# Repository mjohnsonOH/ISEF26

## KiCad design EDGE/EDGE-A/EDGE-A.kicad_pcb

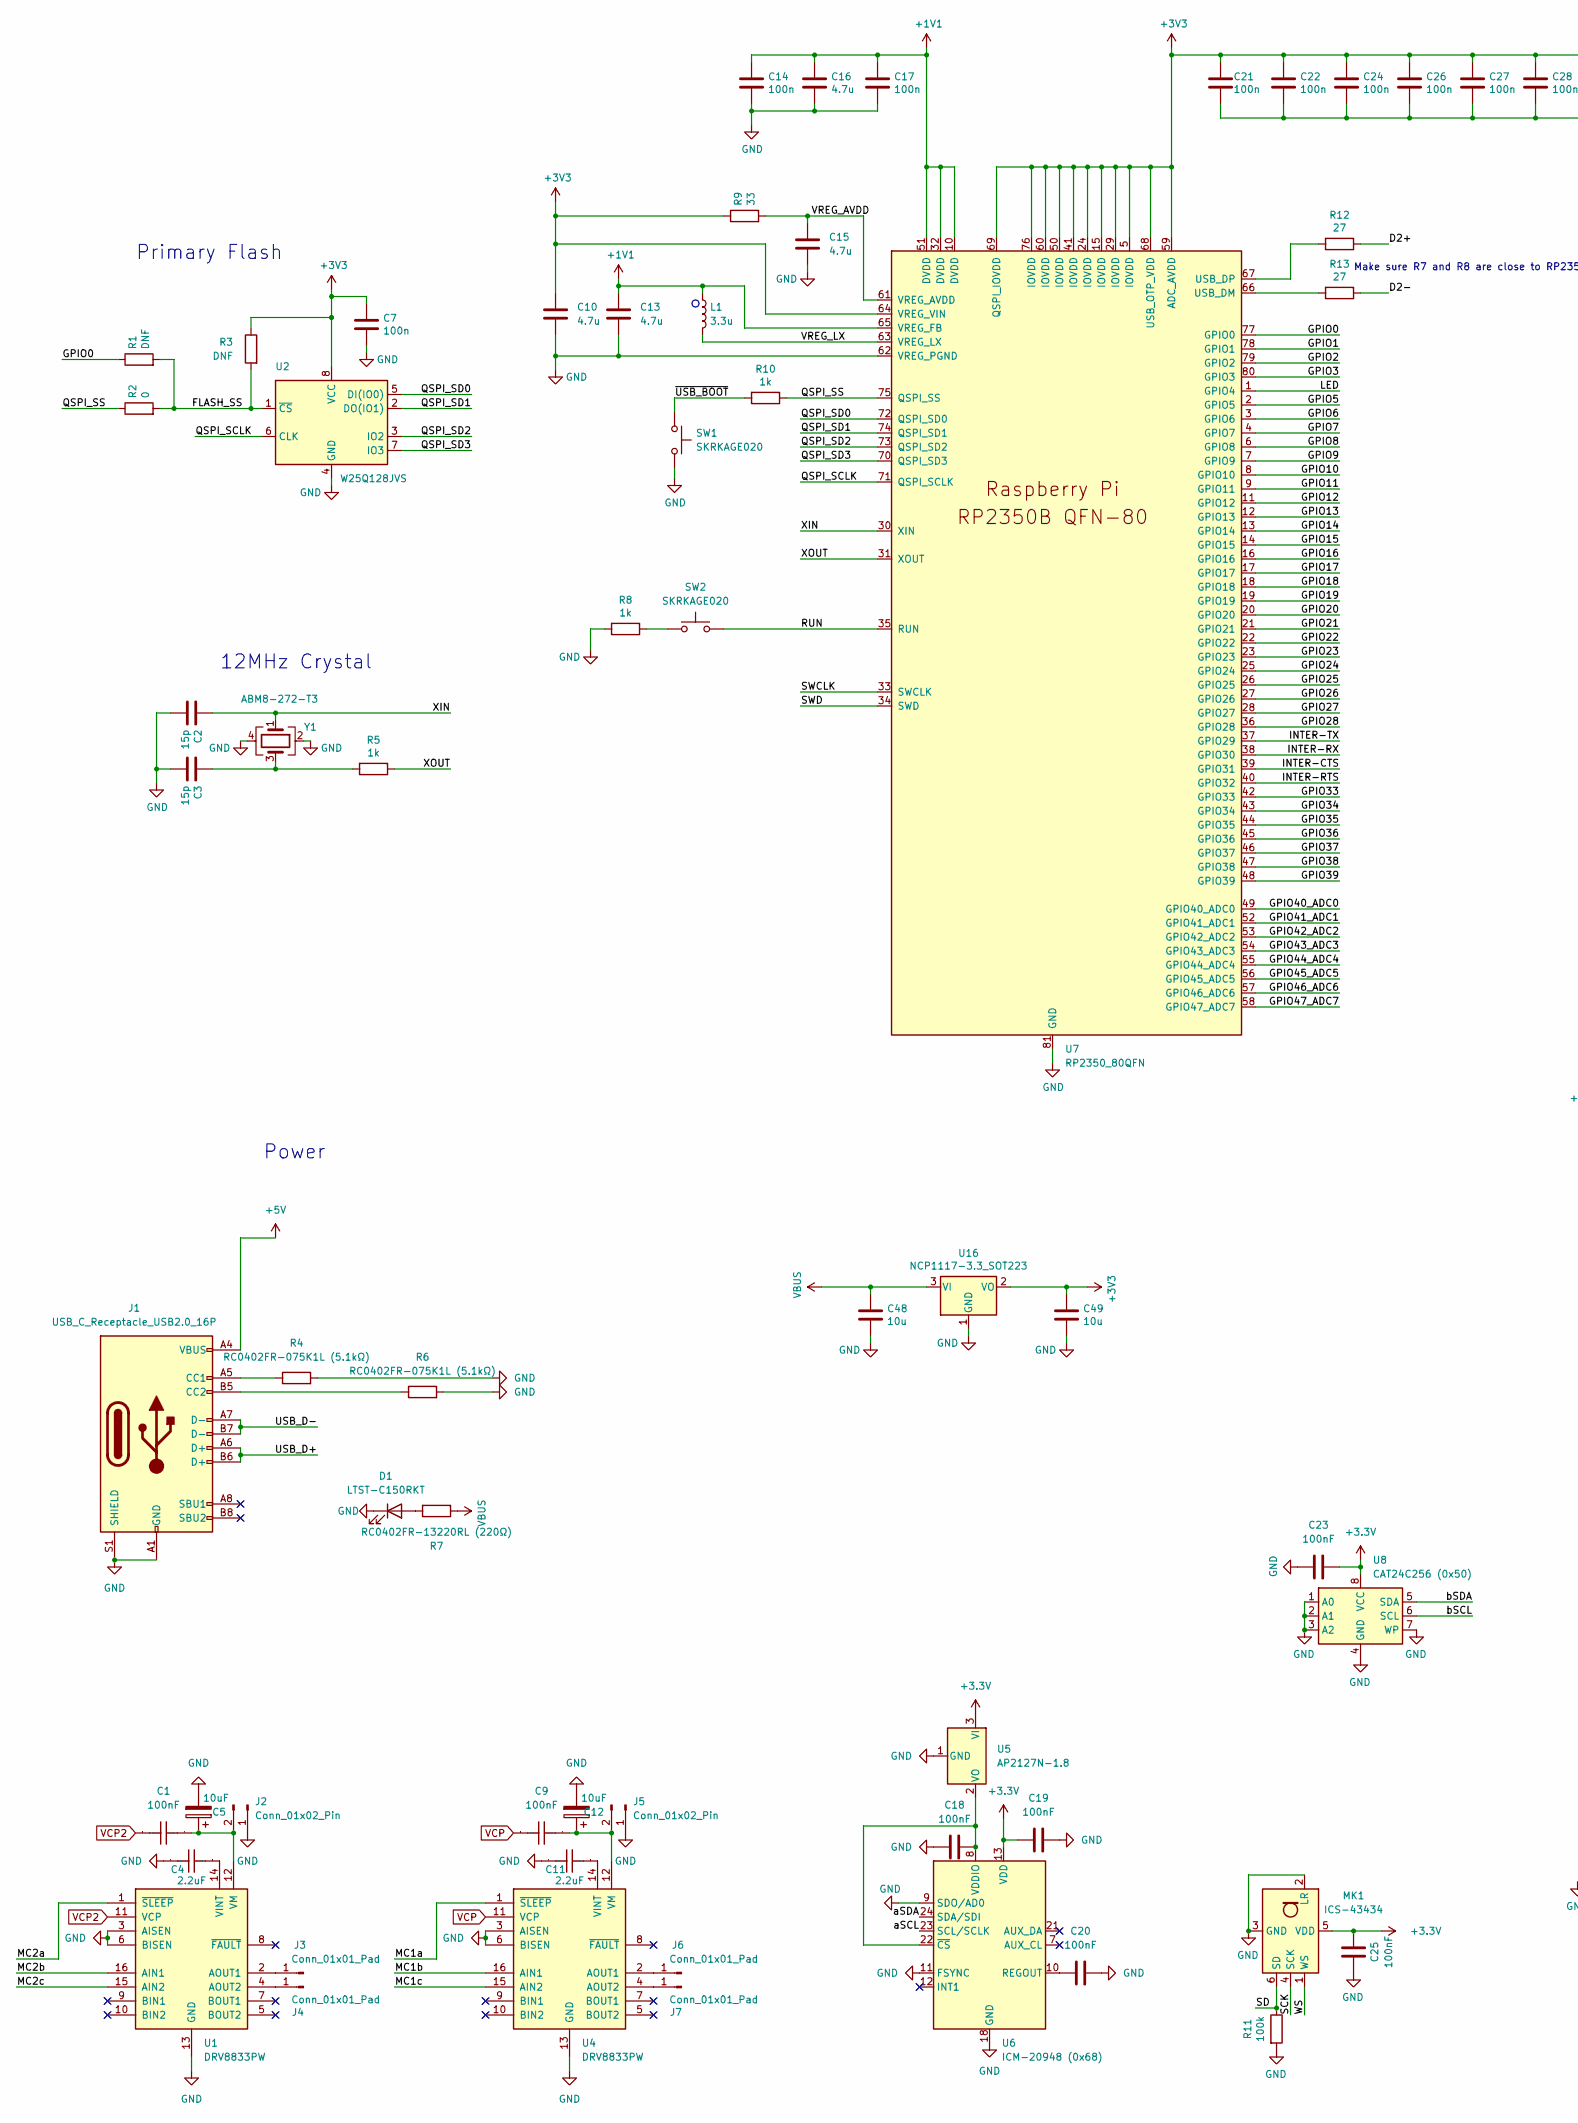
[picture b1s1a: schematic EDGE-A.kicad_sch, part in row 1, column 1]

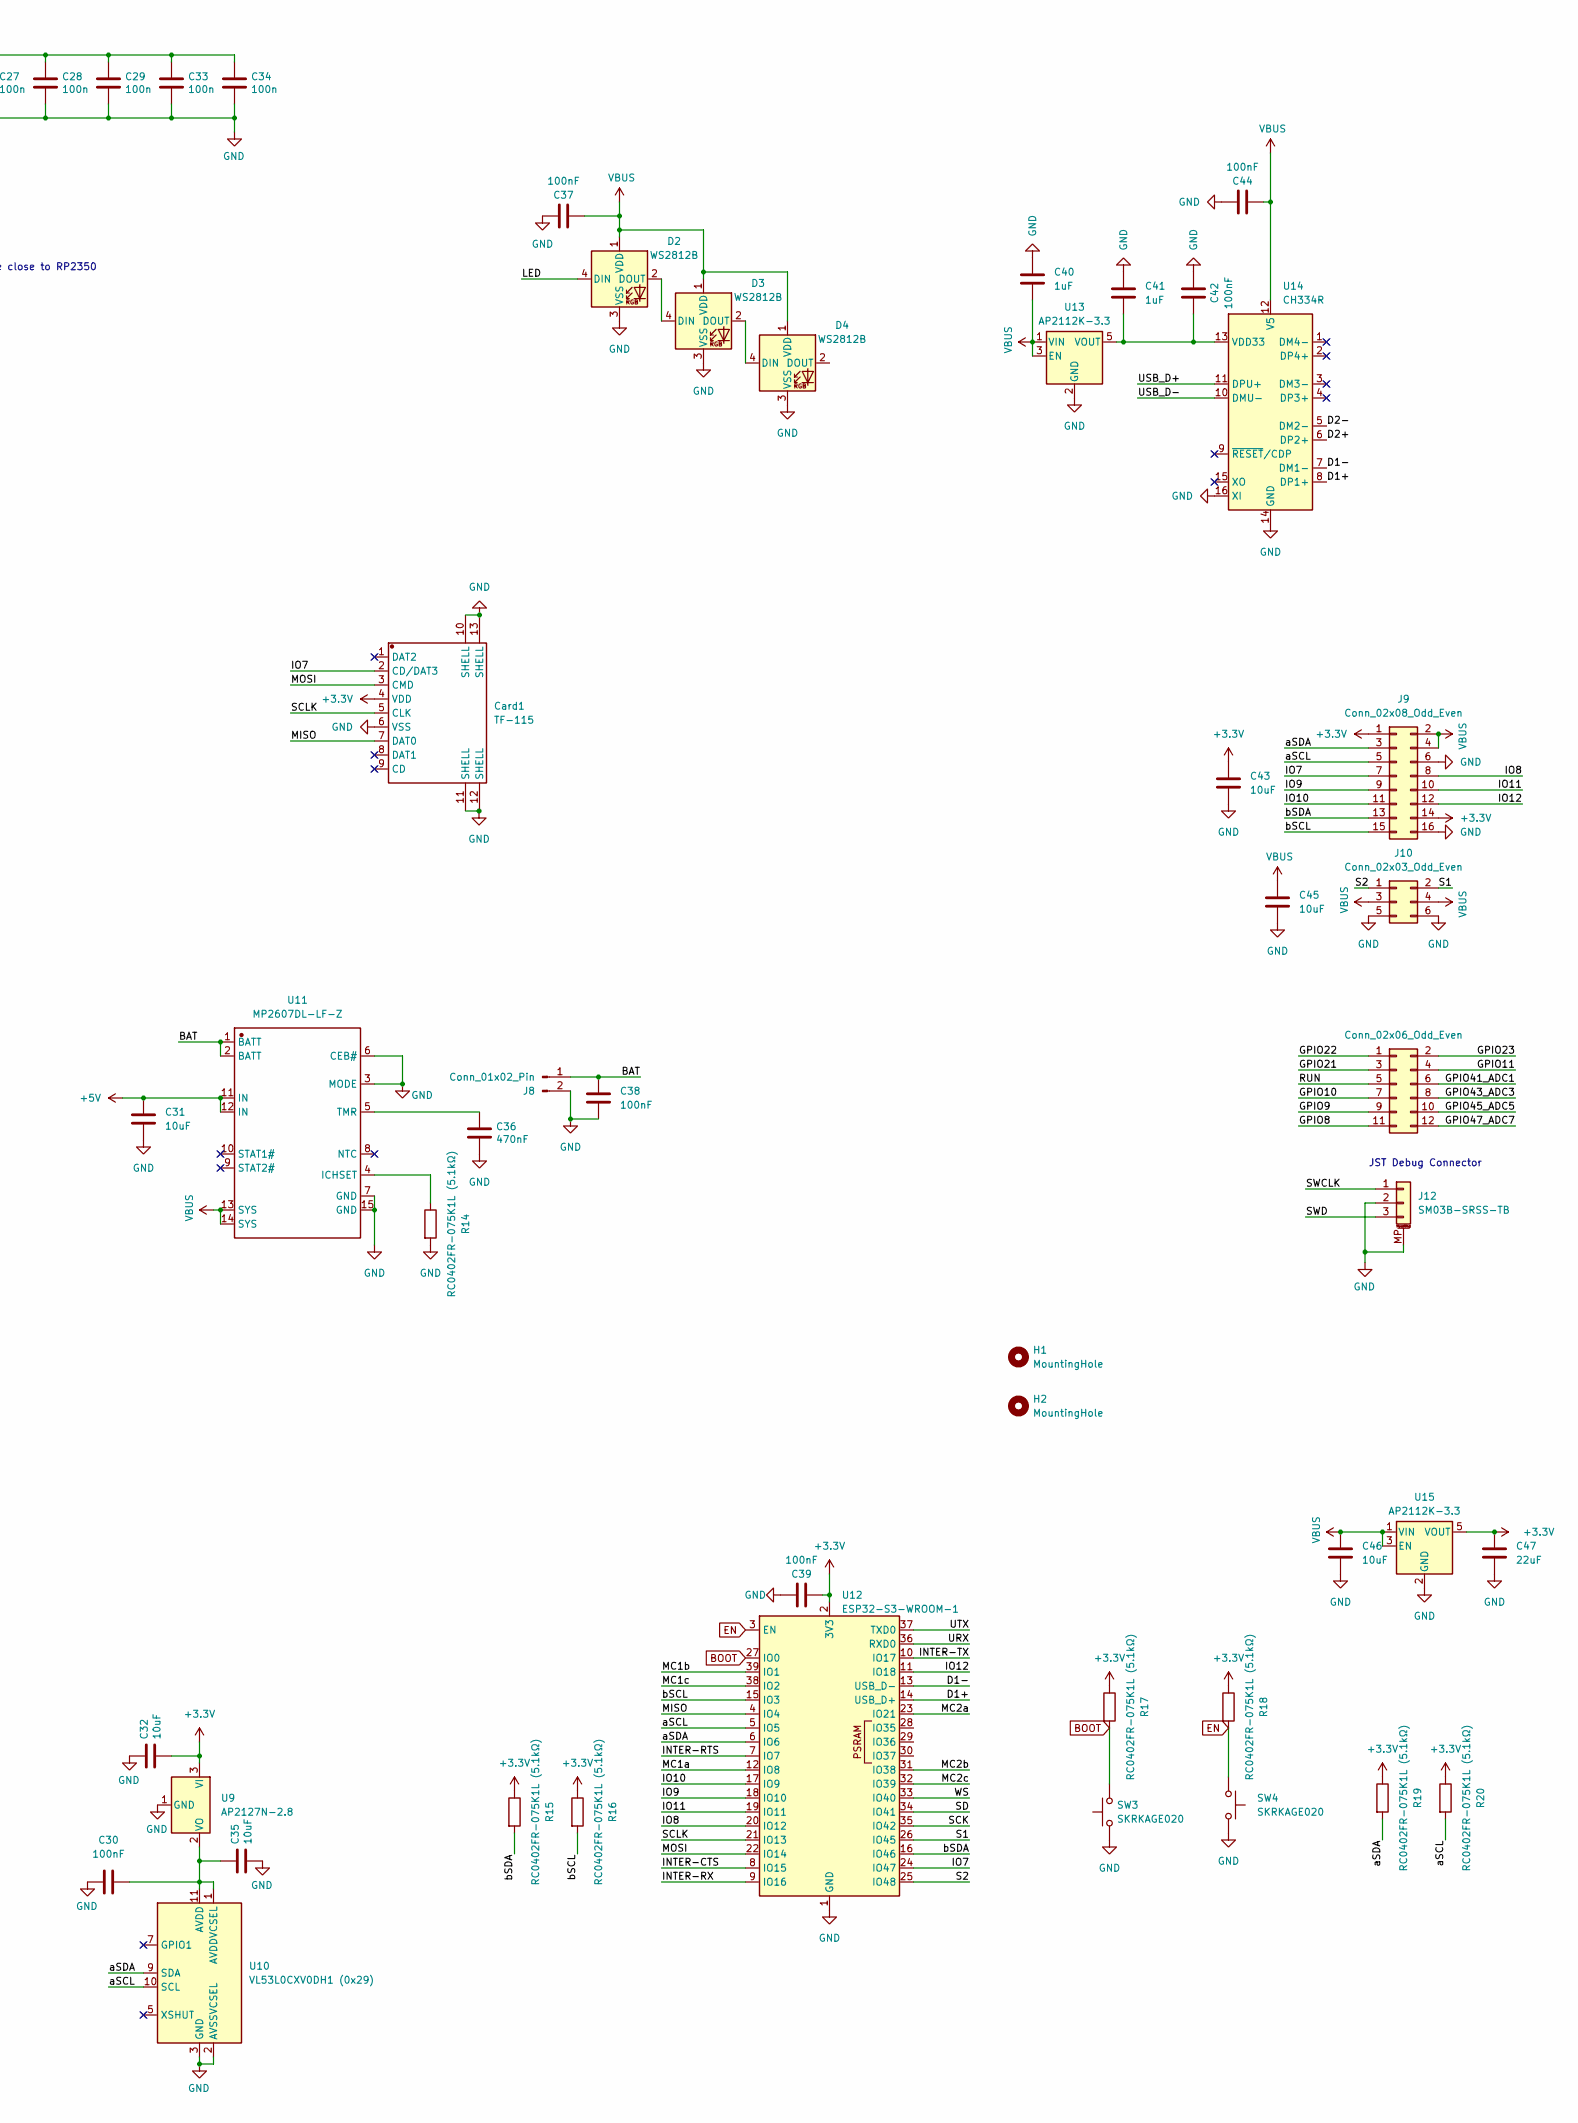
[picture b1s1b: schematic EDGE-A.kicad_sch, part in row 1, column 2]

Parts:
C1, C9: 100nF; CC0805KRX7R9BB104; Manufacturer Part CC0805KRX7R9BB104
C2, C3: 15p; C_0402_1005Metric
C4, C11: 2.2uF; GRM155R60J225KE01D; Manufacturer Part GRM155R60J225KE01D
C5, C12: 10uF; TAJA106K016RNJ
C7, C14, C17, C21, C22, C24, C26, C27, C28, C29, C33, C34: 100n; C_0402_1005Metric
C10, C13: 4.7u; C_0402_1005Metric_small_pads
C15, C16: 4.7u; C_0402_1005Metric
C18, C19, C20, C23, C25, C30, C37, C38, C39, C42, C44: 100nF; C0402
C31, C43, C45, C46: 10uF; C0402
C32, C35: 10uF; C_0805_2012Metric
C36: 470nF; C_0402_1005Metric
C40, C41: 1uF; C0402
C47: 22uF; C0402
C48, C49: 10u; C_0805_2012Metric
Card1: TF-115; TF-SMD_TF-115; Manufacturer Part TF-115
D1: LTST-C150RKT; LED_1206_3216Metric
D2, D3, D4: WS2812B; LED_WS2812B_PLCC4_5.0x5.0mm_P3.2mm
H1, H2: MountingHole; MountingHole_3.2mm_M3
J1: USB_C_Receptacle_USB2.0_16P; USB_C_Receptacle_HCTL_HC-TYPE-C-16P-01A
J2, J5: Conn_01x02_Pin; PinHeader_1x02_P2.54mm_Vertical
J3, J4, J6, J7: Conn_01x01_Pad; TestPoint_Pad_1.5x1.5mm
J8: Conn_01x02_Pin; JST_PH_S2B-PH-K_1x02_P2.00mm_Horizontal
J9: Conn_02x08_Odd_Even; PinHeader_2x08_P2.54mm_Vertical
J10: Conn_02x03_Odd_Even; PinHeader_2x03_P2.54mm_Vertical
J11: Conn_02x06_Odd_Even; PinHeader_2x06_P2.54mm_Vertical
J12: SM03B-SRSS-TB; JST_SH_SM03B-SRSS-TB_1x03-1MP_P1.00mm_Horizontal
L1: 3.3u; L_pol_2016
MK1: ICS-43434; InvenSense_ICS-43434-6_3.5x2.65mm
R1, R3: DNF; R_0402_1005Metric
R2: 0; R_0402_1005Metric
R4, R6, R14, R15, R16, R17, R18, R19, R20: RC0402FR-075K1L (5.1kΩ); R0402
R5, R8, R10: 1k; R_0402_1005Metric
R7: RC0402FR-13220RL (220Ω); R0402
R9: 33; R_0402_1005Metric
R11: 100k; R_0402_1005Metric
R12, R13: 27; R_0402_1005Metric
SW1, SW2, SW3, SW4: SKRKAGE020; SW_Push_SPST_NO_Alps_SKRK
U1, U4: DRV8833PW; TSSOP-16_4.4x5mm_P0.65mm
U2: W25Q128JVS; SOIC-8_5.3x5.3mm_P1.27mm
U5: AP2127N-1.8; SOT-23
U6: ICM-20948 (0x68); InvenSense_QFN-24_3x3mm_P0.4mm
U7: RP2350_80QFN; RP2350-QFN-80-1EP_10x10_P0.4mm_EP3.4x3.4mm_ThermalVias
U8: CAT24C256 (0x50); SOIC-8_3.9x4.9mm_P1.27mm
U9: AP2127N-2.8; SOT-23
U10: VL53L0CXV0DH1 (0x29); ST_VL53L1x
U11: MP2607DL-LF-Z; MP2607DL; Manufacturer Part MP2607DL-LF-Z
U12: ESP32-S3-WROOM-1
U13, U15: AP2112K-3.3; SOT-23-5
U14: CH334R; QSOP-16_3.9x4.9mm_P0.635mm
U16: NCP1117-3.3_SOT223; SOT-223-3_TabPin2
Y1: ABM8-272-T3; Crystal_SMD_3225-4Pin_3.2x2.5mm

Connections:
+1V1: C13.1, C14.1, C16.1, C17.1, L1.1, U7.10 (DVDD), U7.32 (DVDD), U7.51 (DVDD), U7.65 (VREG_FB)
+3.3V: C19.1, C23.1, C25.1, C32.2, C39.2, C43.1, C47.1, Card1.4 (VDD), J9.1, J9.14, MK1.5 (VDD), R15.1, R16.1, R17.1, R18.1, R19.1, R20.1, U5.3 (VI), U6.13 (VDD), U8.8 (VCC), U9.3 (VI), U12.2 (3V3), U15.5 (VOUT)
+3V3: C7.1, C10.1, C21.1, C22.1, C24.1, C26.1, C27.1, C28.1, C29.1, C33.1, C34.1, C49.1, R3.1, R9.1, U2.8 (VCC), U7.5 (IOVDD), U7.15 (IOVDD), U7.24 (IOVDD), U7.29 (IOVDD), U7.41 (IOVDD), U7.50 (IOVDD), U7.59 (ADC_AVDD), U7.60 (IOVDD), U7.64 (VREG_VIN), U7.68 (USB_OTP_VDD), U7.69 (QSPI_IOVDD), U7.76 (IOVDD), U16.2 (VO)
+5V: C31.1, J1.A4 (VBUS), J1.A9 (VBUS), J1.B4 (VBUS), J1.B9 (VBUS), U11.11 (IN), U11.12 (IN)
/BAT: C38.1, J8.1, U11.1 (BATT), U11.2 (BATT)
/D1+: U12.14 (USB_D+), U14.8 (DP1+)
/D1-: U12.13 (USB_D-), U14.7 (DM1-)
/D2+: R12.1, U14.6 (DP2+)
/D2-: R13.1, U14.5 (DM2-)
/FLASH_SS: R1.2, R2.2, R3.2, U2.1 (~CS)
/GPIO0: R1.1, U7.77 (GPIO0)
/GPIO1: U7.78 (GPIO1)
/GPIO2: U7.79 (GPIO2)
/GPIO3: U7.80 (GPIO3)
/GPIO5: U7.2 (GPIO5)
/GPIO6: U7.3 (GPIO6)
/GPIO7: U7.4 (GPIO7)
/GPIO8: J11.11, U7.6 (GPIO8)
/GPIO9: J11.9, U7.7 (GPIO9)
/GPIO10: J11.7, U7.8 (GPIO10)
/GPIO11: J11.4, U7.9 (GPIO11)
/GPIO12: U7.11 (GPIO12)
/GPIO13: U7.12 (GPIO13)
/GPIO14: U7.13 (GPIO14)
/GPIO15: U7.14 (GPIO15)
/GPIO16: U7.16 (GPIO16)
/GPIO17: U7.17 (GPIO17)
/GPIO18: U7.18 (GPIO18)
/GPIO19: U7.19 (GPIO19)
/GPIO20: U7.20 (GPIO20)
/GPIO21: J11.3, U7.21 (GPIO21)
/GPIO22: J11.1, U7.22 (GPIO22)
/GPIO23: J11.2, U7.23 (GPIO23)
/GPIO24: U7.25 (GPIO24)
/GPIO25: U7.26 (GPIO25)
/GPIO26: U7.27 (GPIO26)
/GPIO27: U7.28 (GPIO27)
/GPIO28: U7.36 (GPIO28)
/GPIO33: U7.42 (GPIO33)
/GPIO34: U7.43 (GPIO34)
/GPIO35: U7.44 (GPIO35)
/GPIO36: U7.45 (GPIO36)
/GPIO37: U7.46 (GPIO37)
/GPIO38: U7.47 (GPIO38)
/GPIO39: U7.48 (GPIO39)
/GPIO40_ADC0: U7.49 (GPIO40_ADC0)
/GPIO41_ADC1: J11.6, U7.52 (GPIO41_ADC1)
/GPIO42_ADC2: U7.53 (GPIO42_ADC2)
/GPIO43_ADC3: J11.8, U7.54 (GPIO43_ADC3)
/GPIO44_ADC4: U7.55 (GPIO44_ADC4)
/GPIO45_ADC5: J11.10, U7.56 (GPIO45_ADC5)
/GPIO46_ADC6: U7.57 (GPIO46_ADC6)
/GPIO47_ADC7: J11.12, U7.58 (GPIO47_ADC7)
/INTER-CTS: U7.39 (GPIO31), U12.8 (IO15)
/INTER-RTS: U7.40 (GPIO32), U12.7 (IO7)
/INTER-RX: U7.38 (GPIO30), U12.9 (IO16)
/INTER-TX: U7.37 (GPIO29), U12.10 (IO17)
/IO7: Card1.2 (CD/DAT3), J9.7, U12.24 (IO47)
/IO8: J9.8, U12.20 (IO12)
/IO9: J9.9, U12.18 (IO10)
/IO10: J9.11, U12.17 (IO9)
/IO11: J9.10, U12.19 (IO11)
/IO12: J9.12, U12.11 (IO18)
/LED: D2.4 (DIN), U7.1 (GPIO4)
/MC1a: U4.1 (~SLEEP), U12.12 (IO8)
/MC1b: U4.16 (AIN1), U12.39 (IO1)
/MC1c: U4.15 (AIN2), U12.38 (IO2)
/MC2a: U1.1 (~SLEEP), U12.23 (IO21)
/MC2b: U1.16 (AIN1), U12.31 (IO38)
/MC2c: U1.15 (AIN2), U12.32 (IO39)
/MISO: Card1.7 (DAT0), U12.4 (IO4)
/MOSI: Card1.3 (CMD), U12.22 (IO14)
/QSPI_SCLK: U2.6 (CLK), U7.71 (QSPI_SCLK)
/QSPI_SD0: U2.5 (DI(IO0)), U7.72 (QSPI_SD0)
/QSPI_SD1: U2.2 (DO(IO1)), U7.74 (QSPI_SD1)
/QSPI_SD2: U2.3 (IO2), U7.73 (QSPI_SD2)
/QSPI_SD3: U2.7 (IO3), U7.70 (QSPI_SD3)
/QSPI_SS: R2.1, R10.1, U7.75 (QSPI_SS)
/RUN: J11.5, SW2.2, U7.35 (RUN)
/S1: J10.2, U12.26 (IO45)
/S2: J10.1, U12.25 (IO48)
/SCK: MK1.4 (SCK), U12.35 (IO42)
/SCLK: Card1.5 (CLK), U12.21 (IO13)
/SD: MK1.6 (SD), R11.1, U12.34 (IO41)
/SWCLK: J12.1, U7.33 (SWCLK)
/SWD: J12.3, U7.34 (SWD)
/URX: U12.36 (RXD0)
/USB_D+: J1.A6 (D+), J1.B6 (D+), U14.11 (DPU+)
/USB_D-: J1.A7 (D-), J1.B7 (D-), U14.10 (DMU-)
/UTX: U12.37 (TXD0)
/VREG_AVDD: C15.1, R9.2, U7.61 (VREG_AVDD)
/VREG_LX: L1.2, U7.63 (VREG_LX)
/WS: MK1.1 (WS), U12.33 (IO40)
/XIN: C2.1, U7.30 (XIN), Y1.1
/XOUT: R5.1, U7.31 (XOUT)
/aSCL: J9.5, R20.2, U6.23 (SCL/SCLK), U10.10 (SCL), U12.5 (IO5)
/aSDA: J9.3, R19.2, U6.24 (SDA/SDI), U10.9 (SDA), U12.6 (IO6)
/bSCL: J9.15, R16.2, U8.6 (SCL), U12.15 (IO3)
/bSDA: J9.13, R15.2, U8.5 (SDA), U12.16 (IO46)
/~USB_BOOT: R10.2, SW1.1
BOOT: R17.2, SW3.2, U12.27 (IO0)
EN: R18.2, SW4.1, U12.3 (EN)
GND: C2.2, C3.2, C4.2, C5.2, C7.2, C10.2, C11.2, C12.2, C13.2, C14.2, C15.2, C16.2, C17.2, C18.1, C19.2, C20.2, C21.2, C22.2, C23.2, C24.2, C25.2, C26.2, C27.2, C28.2, C29.2, C30.2, C31.2, C32.1, C33.2, C34.2, C35.2, C36.2, C37.1, C38.2, C39.1, C40.1, C41.1, C42.1, C43.2, C44.1, C45.2, C46.2, C47.2, C48.2, C49.2, Card1.6 (VSS), Card1.10 (SHELL), Card1.11 (SHELL), Card1.12 (SHELL), Card1.13 (SHELL), D1.1 (K), D2.3 (VSS), D3.3 (VSS), D4.3 (VSS), J1.A1 (GND), J1.A12 (GND), J1.B1 (GND), J1.B12 (GND), J1.S1 (SHIELD), J2.1, J5.1, J8.2, J9.6, J9.16, J10.5, J10.6, J12.2, J12.MP (MountPin), MK1.2 (LR), MK1.3 (GND), R4.2, R6.2, R8.2, R11.2, R14.2, SW1.2, SW3.1, SW4.2, U1.3 (AISEN), U1.6 (BISEN), U1.13 (GND), U2.4 (GND), U4.3 (AISEN), U4.6 (BISEN), U4.13 (GND), U5.1 (GND), U6.9 (SDO/AD0), U6.11 (FSYNC), U6.18 (GND), U6.20 (GND), U7.62 (VREG_PGND), U7.81 (GND), U8.1 (A0), U8.2 (A1), U8.3 (A2), U8.4 (GND), U8.7 (WP), U9.1 (GND), U10.2 (AVSSVCSEL), U10.3 (GND), U10.4 (GND), U10.6 (GND), U10.12 (GND), U11.3 (MODE), U11.6 (CEB#), U11.7 (GND), U11.15 (GND), U12.1 (GND), U12.40 (GND), U12.41 (GND), U13.2 (GND), U14.14 (GND), U14.16 (XI), U15.2 (GND), U16.1 (GND), Y1.2, Y1.4
unnamed: C3.1, R5.2, Y1.3
unnamed: D1.2 (A), R7.2
unnamed: D2.2 (DOUT), D3.4 (DIN)
unnamed: D3.2 (DOUT), D4.4 (DIN)
unnamed: J1.A5 (CC1), R4.1
unnamed: J1.B5 (CC2), R6.1
unnamed: C1.2, C5.1, J2.2, U1.12 (VM)
unnamed: J3.1, U1.2 (AOUT1)
unnamed: J4.1, U1.4 (AOUT2)
unnamed: C9.2, C12.1, J5.2, U4.12 (VM)
unnamed: J6.1, U4.2 (AOUT1)
unnamed: J7.1, U4.4 (AOUT2)
unnamed: R8.1, SW2.1
unnamed: C4.1, U1.14 (VINT)
unnamed: C11.1, U4.14 (VINT)
unnamed: C18.2, U5.2 (VO), U6.8 (VDDIO), U6.22 (~CS)
unnamed: C20.1, U6.10 (REGOUT)
unnamed: R13.2, U7.66 (USB_DM)
unnamed: R12.2, U7.67 (USB_DP)
unnamed: C30.1, C35.1, U9.2 (VO), U10.1 (AVDDVCSEL), U10.11 (AVDD)
unnamed: R14.1, U11.4 (ICHSET)
unnamed: C36.1, U11.5 (TMR)
unnamed: C41.2, C42.2, U13.5 (VOUT), U14.13 (VDD33)
VBUS: C37.2, C40.2, C44.2, C45.1, C46.1, C48.1, D2.1 (VDD), D3.1 (VDD), D4.1 (VDD), J9.2, J9.4, J10.3, J10.4, R7.1, U11.13 (SYS), U11.14 (SYS), U13.1 (VIN), U13.3 (EN), U14.12 (V5), U15.1 (VIN), U15.3 (EN), U16.3 (VI)
VCP: C9.1, U4.11 (VCP)
VCP2: C1.1, U1.11 (VCP)

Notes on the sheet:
Power
12MHz Crystal
Make sure R7 and R8 are close to RP2350
JST Debug Connector
Primary Flash

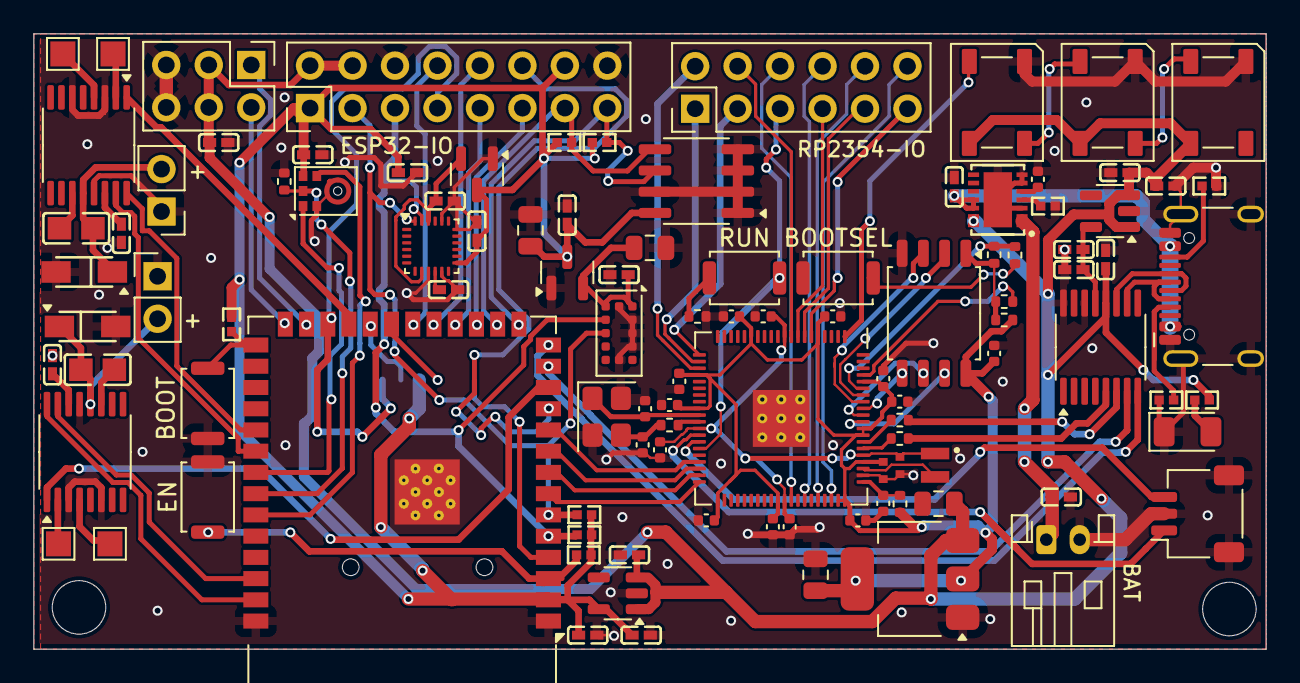
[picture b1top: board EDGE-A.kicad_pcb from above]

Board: 2 copper layers, 73.7 x 36.8 mm, 108 parts (1 on the bottom side), 96 nets.

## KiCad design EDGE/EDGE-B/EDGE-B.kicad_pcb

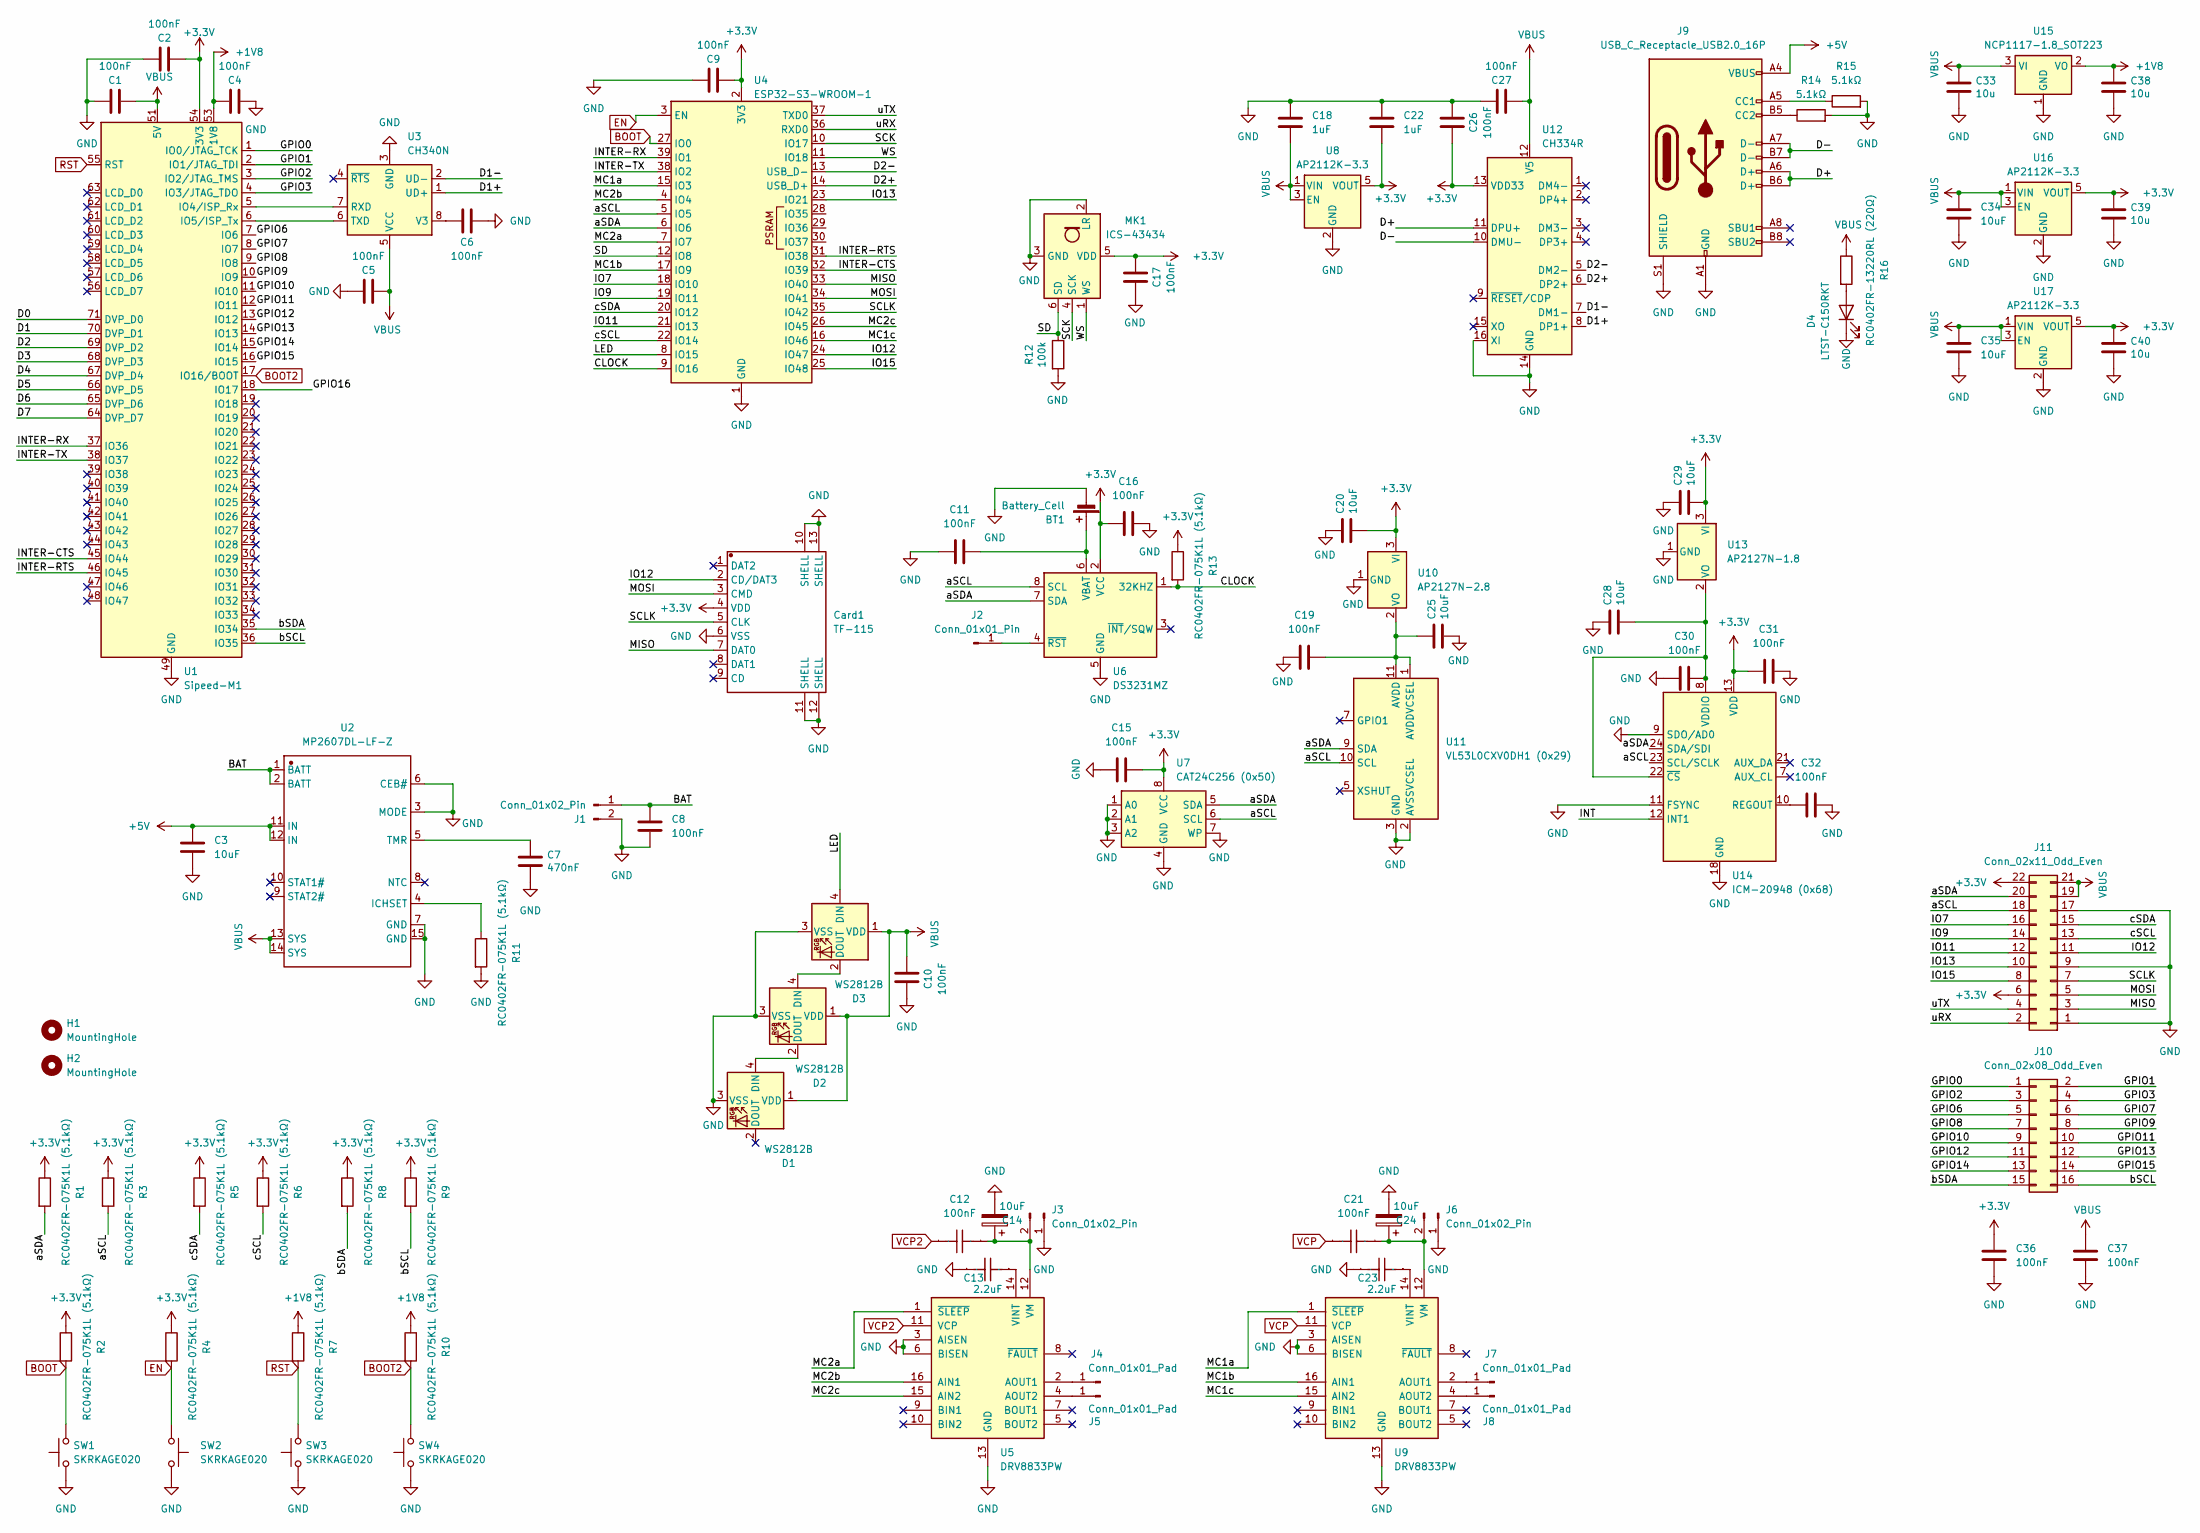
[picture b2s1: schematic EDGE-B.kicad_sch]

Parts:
BT1: Battery_Cell; BatteryHolder_Keystone_3000_1x12mm
C1, C2, C4, C5, C6, C8, C9, C10, C11, C15, C16, C17, C19, C26, C27, C30, C31, C32, C36, C37: 100nF; C0402
C3, C34, C35: 10uF; C0402
C7: 470nF; C_0402_1005Metric
C12, C21: 100nF; CC0805KRX7R9BB104; Manufacturer Part CC0805KRX7R9BB104
C13, C23: 2.2uF; GRM155R60J225KE01D; Manufacturer Part GRM155R60J225KE01D
C14, C24: 10uF; TAJA106K016RNJ
C18, C22: 1uF; C0402
C20, C25, C28, C29: 10uF; C_0805_2012Metric
C33, C38, C39, C40: 10u; C_0805_2012Metric
Card1: TF-115; TF-SMD_TF-115; Manufacturer Part TF-115
D1, D2, D3: WS2812B; LED_WS2812B_PLCC4_5.0x5.0mm_P3.2mm
D4: LTST-C150RKT; LED_1206_3216Metric
H1, H2: MountingHole; MountingHole_3.2mm_M3
J1: Conn_01x02_Pin; JST_PH_S2B-PH-K_1x02_P2.00mm_Horizontal
J2: Conn_01x01_Pin; TestPoint_Pad_1.0x1.0mm
J3, J6: Conn_01x02_Pin; PinHeader_1x02_P2.54mm_Vertical
J4, J5, J7, J8: Conn_01x01_Pad; TestPoint_Pad_1.5x1.5mm
J9: USB_C_Receptacle_USB2.0_16P; USB_C_Receptacle_HCTL_HC-TYPE-C-16P-01A
J10: Conn_02x08_Odd_Even; PinHeader_2x08_P2.54mm_Vertical
J11: Conn_02x11_Odd_Even; PinHeader_2x11_P2.54mm_Vertical
MK1: ICS-43434; InvenSense_ICS-43434-6_3.5x2.65mm
R1, R2, R3, R4, R5, R6, R7, R8, R9, R10, R11, R13: RC0402FR-075K1L (5.1kΩ); R0402
R12: 100k; R_0402_1005Metric
R14, R15: 5.1kΩ; R0402
R16: RC0402FR-13220RL (220Ω); R0402
SW1, SW2, SW3, SW4: SKRKAGE020; SW_Push_SPST_NO_Alps_SKRK
U1: Sipeed-M1
U2: MP2607DL-LF-Z; MP2607DL; Manufacturer Part MP2607DL-LF-Z
U3: CH340N; SOP-8_3.9x4.9mm_P1.27mm
U4: ESP32-S3-WROOM-1
U5, U9: DRV8833PW; TSSOP-16_4.4x5mm_P0.65mm
U6: DS3231MZ; SOIC-8_3.9x4.9mm_P1.27mm
U7: CAT24C256 (0x50); SOIC-8_3.9x4.9mm_P1.27mm
U8, U16, U17: AP2112K-3.3; SOT-23-5
U10: AP2127N-2.8; SOT-23
U11: VL53L0CXV0DH1 (0x29); ST_VL53L1x
U12: CH334R; QSOP-16_3.9x4.9mm_P0.635mm
U13: AP2127N-1.8; SOT-23
U14: ICM-20948 (0x68); InvenSense_QFN-24_3x3mm_P0.4mm
U15: NCP1117-1.8_SOT223; SOT-223-3_TabPin2

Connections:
+1V8: C4.1, C38.1, R7.1, R10.1, U1.53 (1V8), U15.2 (VO)
+3.3V: C2.2, C9.2, C15.1, C16.1, C17.1, C20.2, C22.2, C26.2, C29.2, C31.1, C36.1, C39.1, C40.1, Card1.4 (VDD), J11.6, J11.22, MK1.5 (VDD), R1.1, R2.1, R3.1, R4.1, R5.1, R6.1, R8.1, R9.1, R13.1, U1.54 (3V3), U4.2 (3V3), U6.2 (VCC), U7.8 (VCC), U8.5 (VOUT), U10.3 (VI), U12.13 (VDD33), U13.3 (VI), U14.13 (VDD), U16.5 (VOUT), U17.5 (VOUT)
+5V: C3.1, J9.A4 (VBUS), J9.A9 (VBUS), J9.B4 (VBUS), J9.B9 (VBUS), U2.11 (IN), U2.12 (IN)
/BAT: C8.1, J1.1, U2.1 (BATT), U2.2 (BATT)
/CLOCK: R13.2, U4.9 (IO16), U6.1 (32KHZ)
/D0: U1.71 (DVP_D0)
/D1: U1.70 (DVP_D1)
/D1+: U3.1 (UD+), U12.8 (DP1+)
/D1-: U3.2 (UD-), U12.7 (DM1-)
/D2: U1.69 (DVP_D2)
/D2+: U4.14 (USB_D+), U12.6 (DP2+)
/D2-: U4.13 (USB_D-), U12.5 (DM2-)
/D3: U1.68 (DVP_D3)
/D4: U1.67 (DVP_D4)
/D5: U1.66 (DVP_D5)
/D6: U1.65 (DVP_D6)
/D7: U1.64 (DVP_D7)
/D+: J9.A6 (D+), J9.B6 (D+), U12.11 (DPU+)
/D-: J9.A7 (D-), J9.B7 (D-), U12.10 (DMU-)
/GPIO0: J10.1, U1.1 (IO0/JTAG_TCK)
/GPIO1: J10.2, U1.2 (IO1/JTAG_TDI)
/GPIO2: J10.3, U1.3 (IO2/JTAG_TMS)
/GPIO3: J10.4, U1.4 (IO3/JTAG_TDO)
/GPIO6: J10.5, U1.7 (IO6)
/GPIO7: J10.6, U1.8 (IO7)
/GPIO8: J10.7, U1.9 (IO8)
/GPIO9: J10.8, U1.10 (IO9)
/GPIO10: J10.9, U1.11 (IO10)
/GPIO11: J10.10, U1.12 (IO11)
/GPIO12: J10.11, U1.13 (IO12)
/GPIO13: J10.12, U1.14 (IO13)
/GPIO14: J10.13, U1.15 (IO14)
/GPIO15: J10.14, U1.16 (IO15)
/GPIO16: U1.18 (IO17)
/INT: U14.12 (INT1)
/INTER-CTS: U1.45 (IO44), U4.32 (IO39)
/INTER-RTS: U1.46 (IO45), U4.31 (IO38)
/INTER-RX: U1.37 (IO36), U4.39 (IO1)
/INTER-TX: U1.38 (IO37), U4.38 (IO2)
/IO7: J11.16, U4.18 (IO10)
/IO9: J11.14, U4.19 (IO11)
/IO11: J11.12, U4.21 (IO13)
/IO12: Card1.2 (CD/DAT3), J11.11, U4.24 (IO47)
/IO13: J11.10, U4.23 (IO21)
/IO15: J11.8, U4.25 (IO48)
/LED: D3.4 (DIN), U4.8 (IO15)
/MC1a: U4.15 (IO3), U9.1 (~SLEEP)
/MC1b: U4.17 (IO9), U9.16 (AIN1)
/MC1c: U4.16 (IO46), U9.15 (AIN2)
/MC2a: U4.7 (IO7), U5.1 (~SLEEP)
/MC2b: U4.4 (IO4), U5.16 (AIN1)
/MC2c: U4.26 (IO45), U5.15 (AIN2)
/MISO: Card1.7 (DAT0), J11.3, U4.33 (IO40)
/MOSI: Card1.3 (CMD), J11.5, U4.34 (IO41)
/SCK: MK1.4 (SCK), U4.10 (IO17)
/SCLK: Card1.5 (CLK), J11.7, U4.35 (IO42)
/SD: MK1.6 (SD), R12.1, U4.12 (IO8)
/WS: MK1.1 (WS), U4.11 (IO18)
/aSCL: J11.18, R3.2, U4.5 (IO5), U6.8 (SCL), U7.6 (SCL), U11.10 (SCL), U14.23 (SCL/SCLK)
/aSDA: J11.20, R1.2, U4.6 (IO6), U6.7 (SDA), U7.5 (SDA), U11.9 (SDA), U14.24 (SDA/SDI)
/bSCL: J10.16, R9.2, U1.36 (IO35)
/bSDA: J10.15, R8.2, U1.35 (IO34)
/cSCL: J11.13, R6.2, U4.22 (IO14)
/cSDA: J11.15, R5.2, U4.20 (IO12)
/uRX: J11.2, U4.36 (RXD0)
/uTX: J11.4, U4.37 (TXD0)
BOOT: R2.2, SW1.2, U4.27 (IO0)
BOOT2: R10.2, SW4.2, U1.17 (IO16/BOOT)
EN: R4.2, SW2.1, U4.3 (EN)
GND: BT1.2 (-), C1.1, C2.1, C3.2, C4.2, C5.1, C6.1, C7.2, C8.2, C9.1, C10.1, C11.2, C13.2, C14.2, C15.2, C16.2, C17.2, C18.1, C19.2, C20.1, C22.1, C23.2, C24.2, C25.2, C26.1, C27.1, C28.1, C29.1, C30.1, C31.2, C32.2, C33.2, C34.2, C35.2, C36.2, C37.1, C38.2, C39.2, C40.2, Card1.6 (VSS), Card1.10 (SHELL), Card1.11 (SHELL), Card1.12 (SHELL), Card1.13 (SHELL), D1.3 (VSS), D2.3 (VSS), D3.3 (VSS), D4.1 (K), J1.2, J3.1, J6.1, J9.A1 (GND), J9.A12 (GND), J9.B1 (GND), J9.B12 (GND), J9.S1 (SHIELD), J11.1, J11.9, J11.17, MK1.2 (LR), MK1.3 (GND), R11.2, R12.2, R14.2, R15.2, SW1.1, SW2.2, SW3.1, SW4.1, U1.49 (GND), U1.50 (GND), U1.72 (GND), U2.3 (MODE), U2.6 (CEB#), U2.7 (GND), U2.15 (GND), U3.3 (GND), U4.1 (GND), U4.40 (GND), U4.41 (GND), U5.3 (AISEN), U5.6 (BISEN), U5.13 (GND), U6.5 (GND), U7.1 (A0), U7.2 (A1), U7.3 (A2), U7.4 (GND), U7.7 (WP), U8.2 (GND), U9.3 (AISEN), U9.6 (BISEN), U9.13 (GND), U10.1 (GND), U11.2 (AVSSVCSEL), U11.3 (GND), U11.4 (GND), U11.6 (GND), U11.12 (GND), U12.14 (GND), U12.16 (XI), U13.1 (GND), U14.9 (SDO/AD0), U14.11 (FSYNC), U14.18 (GND), U14.20 (GND), U15.1 (GND), U16.2 (GND), U17.2 (GND)
unnamed: BT1.1 (+), C11.1, U6.6 (VBAT)
unnamed: D1.4 (DIN), D2.2 (DOUT)
unnamed: D2.4 (DIN), D3.2 (DOUT)
unnamed: D4.2 (A), R16.2
unnamed: J2.1, U6.4 (~RST)
unnamed: C12.2, C14.1, J3.2, U5.12 (VM)
unnamed: J4.1, U5.2 (AOUT1)
unnamed: J5.1, U5.4 (AOUT2)
unnamed: C21.2, C24.1, J6.2, U9.12 (VM)
unnamed: J7.1, U9.2 (AOUT1)
unnamed: J8.1, U9.4 (AOUT2)
unnamed: J9.A5 (CC1), R15.1
unnamed: J9.B5 (CC2), R14.1
unnamed: U1.5 (IO4/ISP_Rx), U3.7 (RXD)
unnamed: U1.6 (IO5/ISP_Tx), U3.6 (TXD)
unnamed: R11.1, U2.4 (ICHSET)
unnamed: C7.1, U2.5 (TMR)
unnamed: C6.2, U3.8 (V3)
unnamed: C13.1, U5.14 (VINT)
unnamed: C23.1, U9.14 (VINT)
unnamed: C19.1, C25.1, U10.2 (VO), U11.1 (AVDDVCSEL), U11.11 (AVDD)
unnamed: C28.2, C30.2, U13.2 (VO), U14.8 (VDDIO), U14.22 (~CS)
unnamed: C32.1, U14.10 (REGOUT)
RST: R7.2, SW3.2, U1.55 (RST)
VBUS: C1.2, C5.2, C10.2, C18.2, C27.2, C33.1, C34.1, C35.1, C37.2, D1.1 (VDD), D2.1 (VDD), D3.1 (VDD), J11.19, J11.21, R16.1, U1.51 (5V), U1.52 (5V), U2.13 (SYS), U2.14 (SYS), U3.5 (VCC), U8.1 (VIN), U8.3 (EN), U12.12 (V5), U15.3 (VI), U16.1 (VIN), U16.3 (EN), U17.1 (VIN), U17.3 (EN)
VCP: C21.1, U9.11 (VCP)
VCP2: C12.1, U5.11 (VCP)

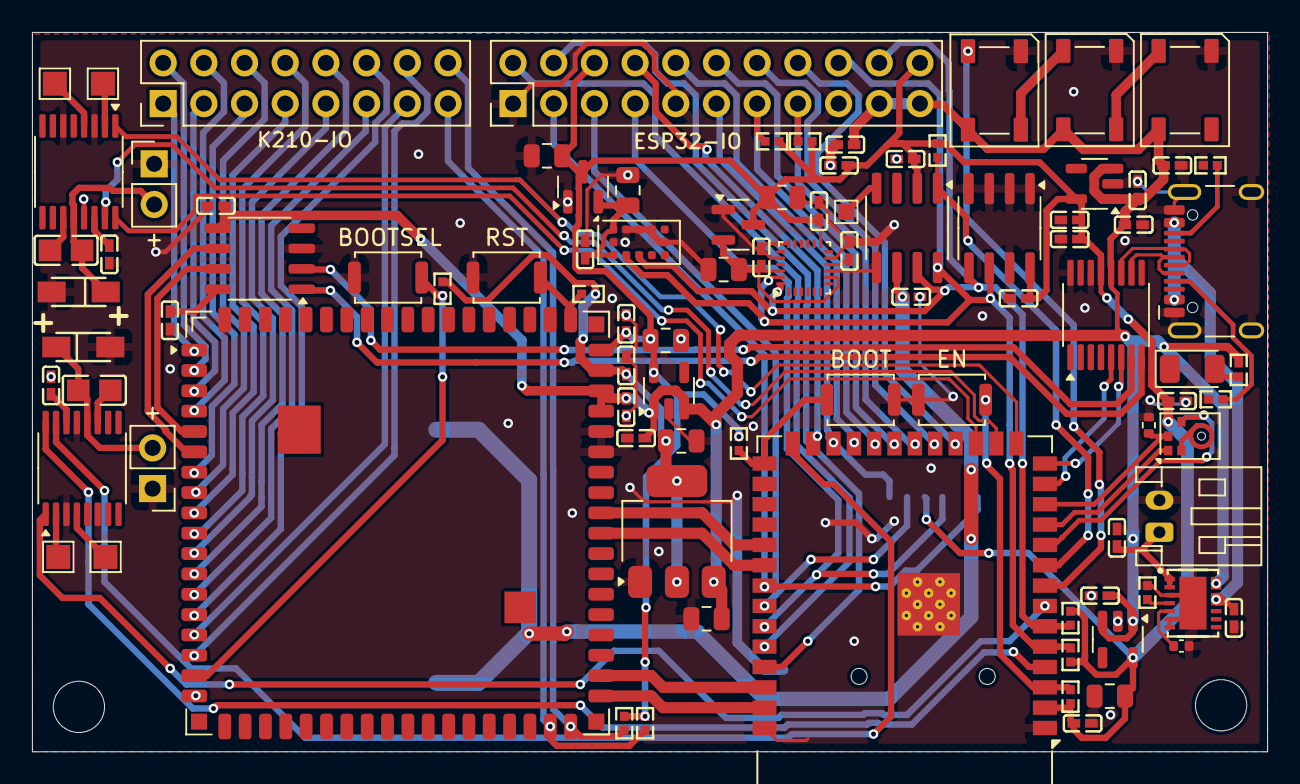
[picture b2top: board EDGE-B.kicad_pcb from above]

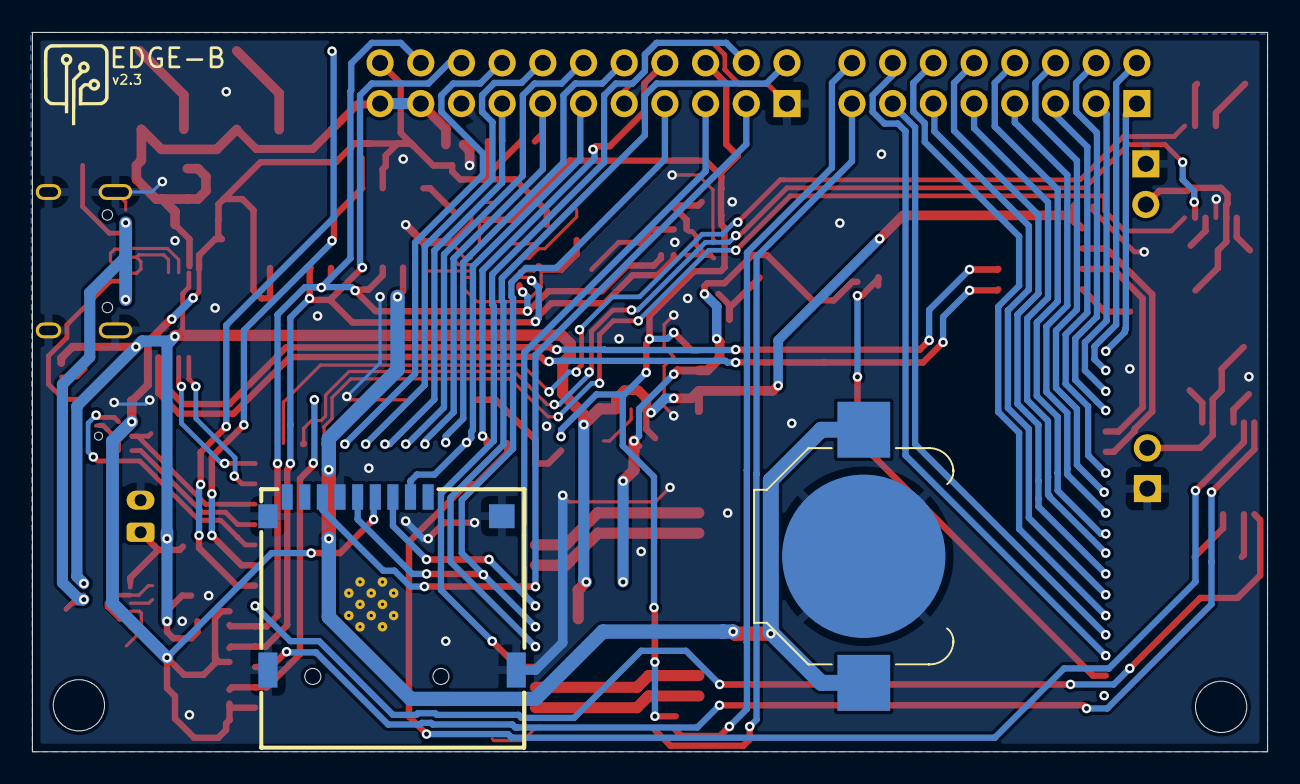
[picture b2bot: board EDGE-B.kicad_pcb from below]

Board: 2 copper layers, 77.1 x 44.9 mm, 97 parts (2 on the bottom side), 87 nets.
